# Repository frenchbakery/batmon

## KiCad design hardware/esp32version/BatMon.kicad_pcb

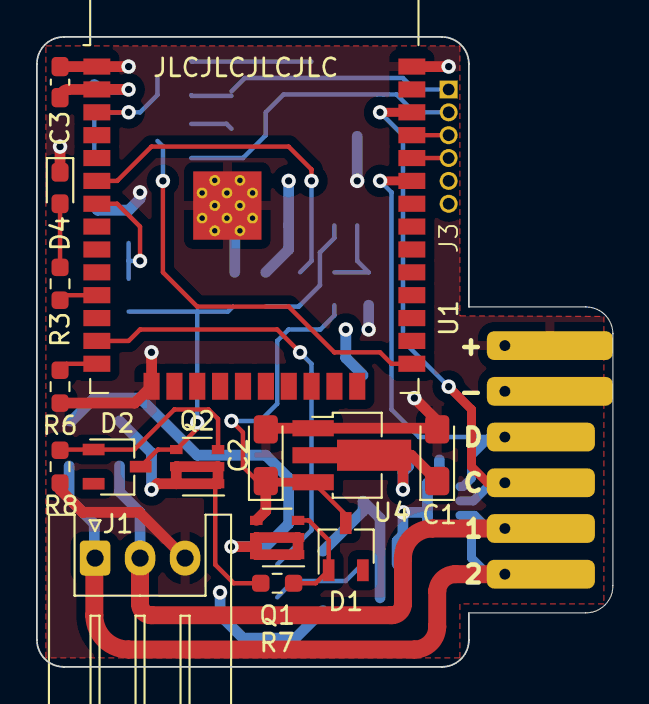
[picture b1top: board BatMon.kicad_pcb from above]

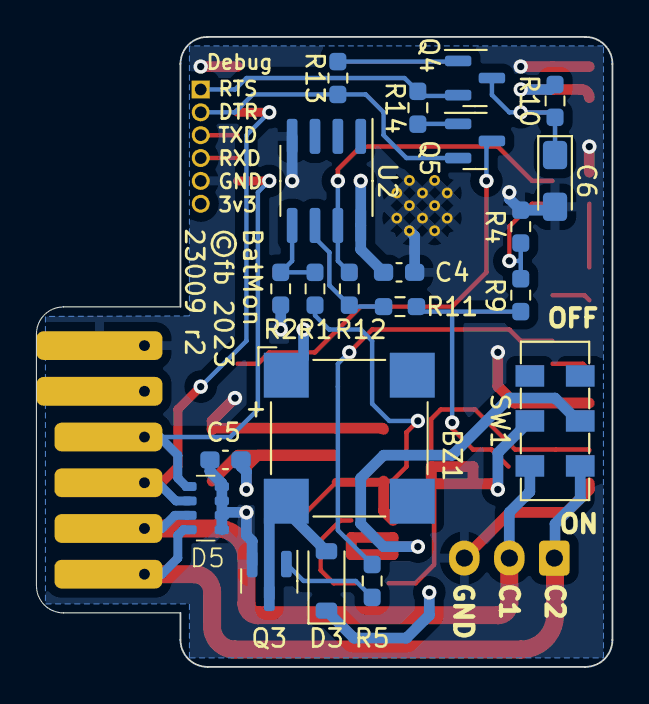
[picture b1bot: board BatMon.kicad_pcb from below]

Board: 4 copper layers, 32.0 x 35.0 mm, 38 parts (21 on the bottom side), 30 nets.

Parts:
BZ1: Buzzer; MagneticBuzzer_CUI_CMT-8504-100-SMT
C1, C2, C6: 22µ; CP_EIA-3216-18_Kemet-A_Pad1.58x1.35mm_HandSolder
C3, C4, C5: 100n; C_0603_1608Metric_Pad1.08x0.95mm_HandSolder
D1, D2: D_Zener_ANK; TSOT-23
D3: D_Schottky; D_SOD-123
D4: LED; LED_0603_1608Metric_Pad1.05x0.95mm_HandSolder
D5: D_TVS_Quad_Array_1206
J1: Battery_Connector; JST_XH_S3B-XH-A_1x03_P2.50mm_Horizontal
J3: Prog_Connector; Dbg_Port_1x6_P1.27mm_ThroughHole
J5: Charging_Connector; Conn_Edge_1x6_LLSSSS_Mirrored
Q1, Q2: Q_PMOS_DDGSDD_TSOP-6; TSOP-6_1.65x3.05mm_P0.95mm
Q3, Q4, Q5: SS8050-G; SOT-23
R1, R11: 30k; R_0603_1608Metric_Pad0.98x0.95mm_HandSolder
R2, R4, R6, R10, R12, R13, R14: 10k; R_0603_1608Metric_Pad0.98x0.95mm_HandSolder
R3, R5, R7, R8: 330; R_0603_1608Metric_Pad0.98x0.95mm_HandSolder
R9: 20k; R_0603_1608Metric_Pad0.98x0.95mm_HandSolder
SW1: POWER_SW; SW_DPDT_Nidec_CL-SB-22A-1x
U1: ESP32-WROOM-32D
U2: LM2904; SOIC-8_3.9x4.9mm_P1.27mm
U4: AZ1117CR-3.3; SOT-89-3_Handsoldering

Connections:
+3.3V: BZ1.1 (-), C1.1, C3.1, C4.1, C5.1, D3.1 (K), J3.6, J5.2, R10.2, U1.2 (VDD), U2.8 (V+), U4.2 (VO)
/C1RAW: D5.3 (A1), J1.2, J5.5, SW1.1 (A)
/C2RAW: D5.4 (A1), J1.1, J5.6, SW1.4 (A)
/RXD: J3.4, U1.34 (RXD0/IO3)
/TXD: J3.3, U1.35 (TXD0/IO1)
Buzzer: R5.2, U1.13 (IO14)
C1ADC: R4.1, R9.2, U1.7 (IO35)
C1IN: D2.3 (K), Q2.4 (S), R9.1, R11.2
C2ADC: R12.1, U1.6 (IO34), U2.7
C2IN: C2.1, D1.3 (K), Q1.4 (S), R1.2, U4.3 (VI)
ESP_EN: C6.1, Q4.3 (C), R10.1, U1.3 (EN)
ESP_IO0: Q5.3 (C), U1.25 (IO0)
GND: C1.2, C2.2, C3.2, C4.2, C5.2, C6.2, D4.1 (K), D5.5 (A2), D5.6 (A2), D5.7 (A2), D5.8 (A2), J1.3, J3.5, J5.1, Q3.2 (E), R2.2, R4.2, R6.2, R8.1, U1.1 (GND), U1.15 (GND), U1.38 (GND), U1.39 (GND), U2.4 (V-), U4.1 (GND)
unnamed: BZ1.2 (+), D3.2 (A), Q3.3 (C)
unnamed: D4.2 (A), R3.1
unnamed: D1.1 (A), Q1.3 (G), R7.2
unnamed: D2.1 (A), Q2.3 (G), R8.2
unnamed: Q3.1 (B), R5.1
unnamed: Q4.1 (B), R13.1
unnamed: Q5.1 (B), R14.1
unnamed: Q2.1 (D), Q2.2 (D), Q2.5 (D), Q2.6 (D), R7.1, SW1.2 (B)
unnamed: Q1.1 (D), Q1.2 (D), Q1.5 (D), Q1.6 (D), SW1.5 (B)
unnamed: R6.1, U1.14 (IO12)
unnamed: R3.2, U1.11 (IO26)
unnamed: R1.1, R2.1, U2.5 (+)
unnamed: R11.1, R12.2, U2.6 (-)
PROG_DTR: J3.2, Q5.2 (E), R13.2
PROG_RTS: J3.1, Q4.2 (E), R14.2
SCL: D5.2 (A1), J5.4, U1.36 (IO22)
SDA: D5.1 (A1), J5.3, U1.33 (IO21)

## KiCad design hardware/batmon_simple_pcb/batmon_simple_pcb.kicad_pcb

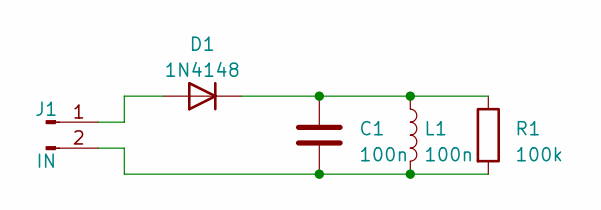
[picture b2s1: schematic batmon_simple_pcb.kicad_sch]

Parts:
C1: 100n; C_0603_1608Metric_Pad1.08x0.95mm_HandSolder
D1: 1N4148; D_MicroMELF
J1: IN; PinHeader_1x02_P2.54mm_Horizontal
L1: 100n; L_Bourns-SRN4018
R1: 100k; R_0603_1608Metric_Pad0.98x0.95mm_HandSolder

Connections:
unnamed: D1.2 (A), J1.1
unnamed: C1.1, D1.1 (K), L1.1, R1.1
unnamed: C1.2, J1.2, L1.2, R1.2

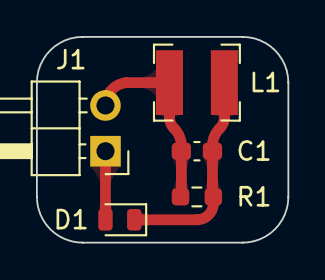
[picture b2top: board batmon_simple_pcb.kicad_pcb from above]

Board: 2 copper layers, 14.0 x 11.4 mm, 5 parts (0 on the bottom side), 3 nets.

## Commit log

2023-04-15 added test circuit for kicad 7
2023-04-27 test version
2023-05-27 pushed some old backup
2023-05-30 started refactoring esp32 batmon
2023-05-31 cleaned up schematic
2023-06-01 added propper el_kicad_libs
2023-06-01 reverse polarity zeners now correct pinout
2023-06-01 updated PCB
2023-06-01 no changes
2023-06-01 implemented new analog section, started component selection process
2023-06-02 worked on schematic and part selection
2023-06-02 started working on new layout
2023-06-02 first iteration of new pcb done
2023-06-02 minor changes, round corners
2023-06-03 added a switch and fixed the battery pinout
2023-06-03 finalized design and exported gerbers
2023-06-03 added part fields and bom
2023-06-05 increased minimal via sizing to reduce cost
2023-06-28 pio project setup
2023-06-28 added blink
2023-06-28 got test code to work
2023-06-28 test proGram for batmon
2023-06-28 fixed battery inputs being connected to non ADC pins on uC (new board revision)
2023-06-28 renamed firmware to test firmware
2023-07-02 new pinouts
2023-07-02 added safe config of invalid pins in test_firmware
2023-07-03 started implementing tetris player
2023-07-03 tetris working
2023-07-03 added project for proper firmware (esp-idf)
2023-07-03 added c++ component
2023-07-03 attempted to work with c++ esp idf component
2023-07-03 got LED blinking to work with normal esp idf, scrapped c++ component
2023-07-03 added gpio doc link
2023-07-04 implemented LED driver with task
2023-07-04 tested LED blinking and adjusted blink timing
2023-07-04 updated programming connector to correct mouser component
2023-07-04 updated to idf version 5.0
2023-07-04 got ADC to work
2023-07-04 adc calibration working
2023-07-05 created a proper battery module
2023-07-05 used multi sampling of cell voltage
2023-07-05 implemented basic buzzer tones
2023-07-05 added buzzer startup sound
2023-07-06 added support for settings stored in NVS
2023-07-06 attempted to implement proper behaviour, but task deletion causes unpredictable crashes
2023-07-06 restructured buzzer and led drivers to work more cleanly and use task notifications instead of deleting tasks over and over again. Buzzer and LED are not working properly
2023-07-06 adjusted timing of notice alive blink mode
2023-07-06 removed test code
2023-07-06 added networking cu
2023-07-10 got wifi and http working (still bad http code)
2023-07-11 added nlohmann json
2023-07-11 got wifi reconnect and HTTP request cycle working properly
2023-07-11 now sending real data over HTTP

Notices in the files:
hardware/esp32version/BatMon.kicad_pcb:
©fb 2023
